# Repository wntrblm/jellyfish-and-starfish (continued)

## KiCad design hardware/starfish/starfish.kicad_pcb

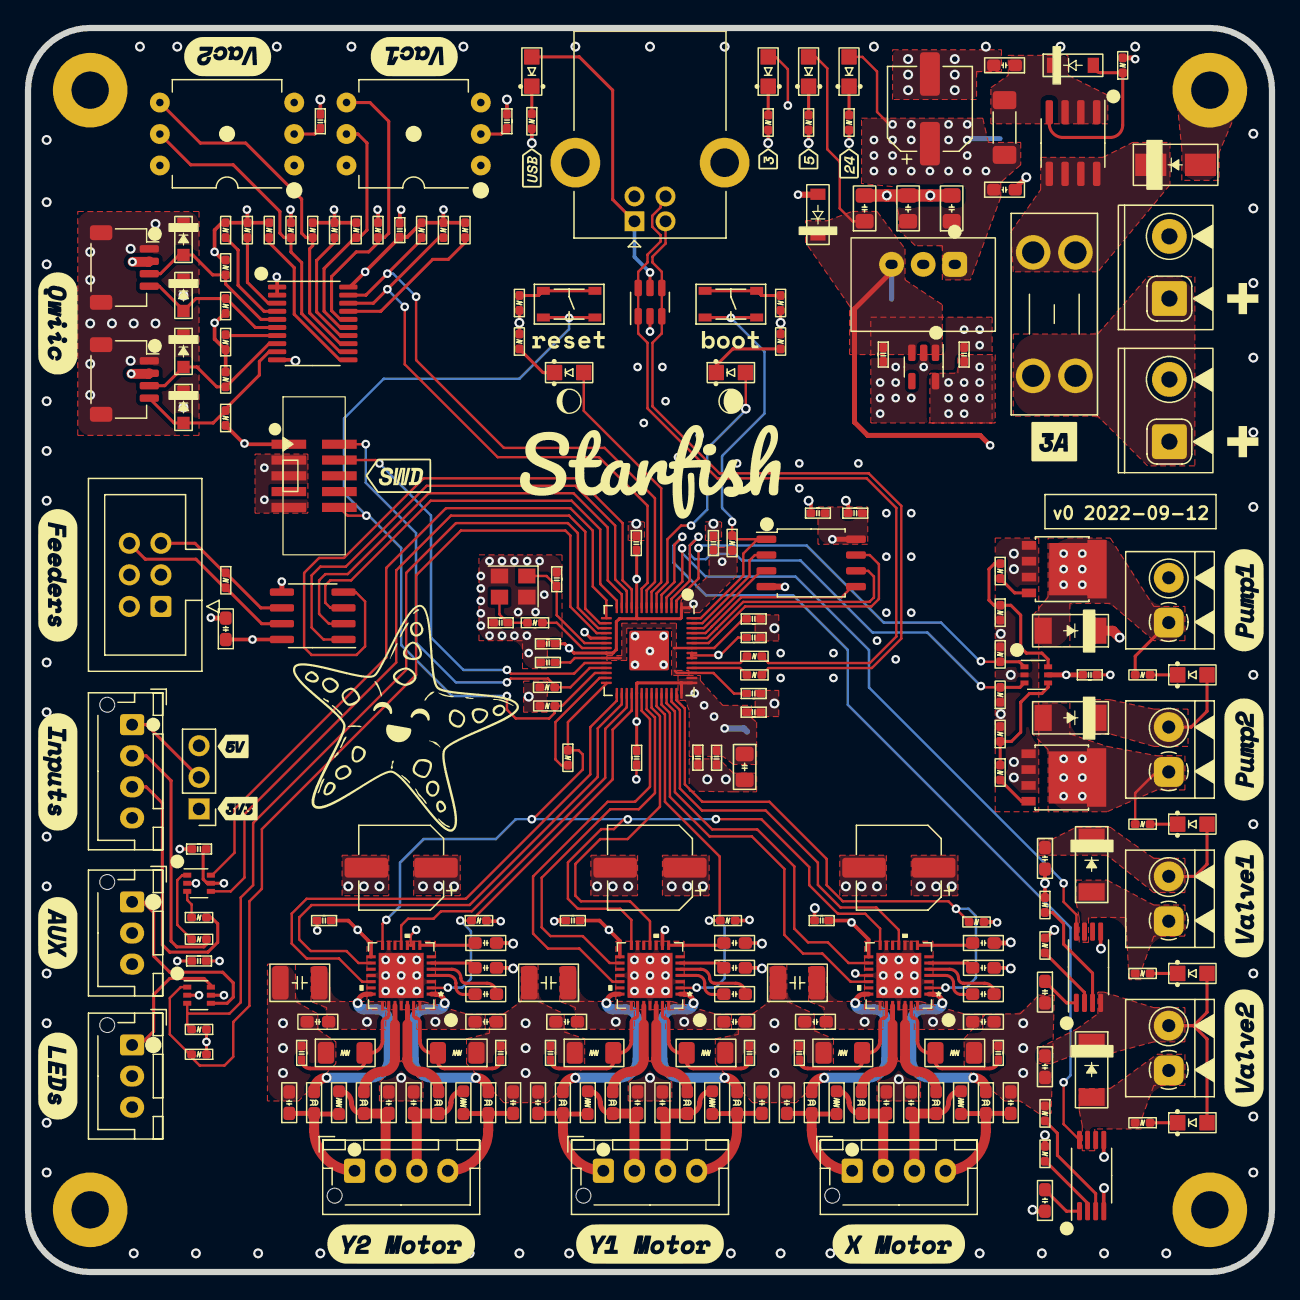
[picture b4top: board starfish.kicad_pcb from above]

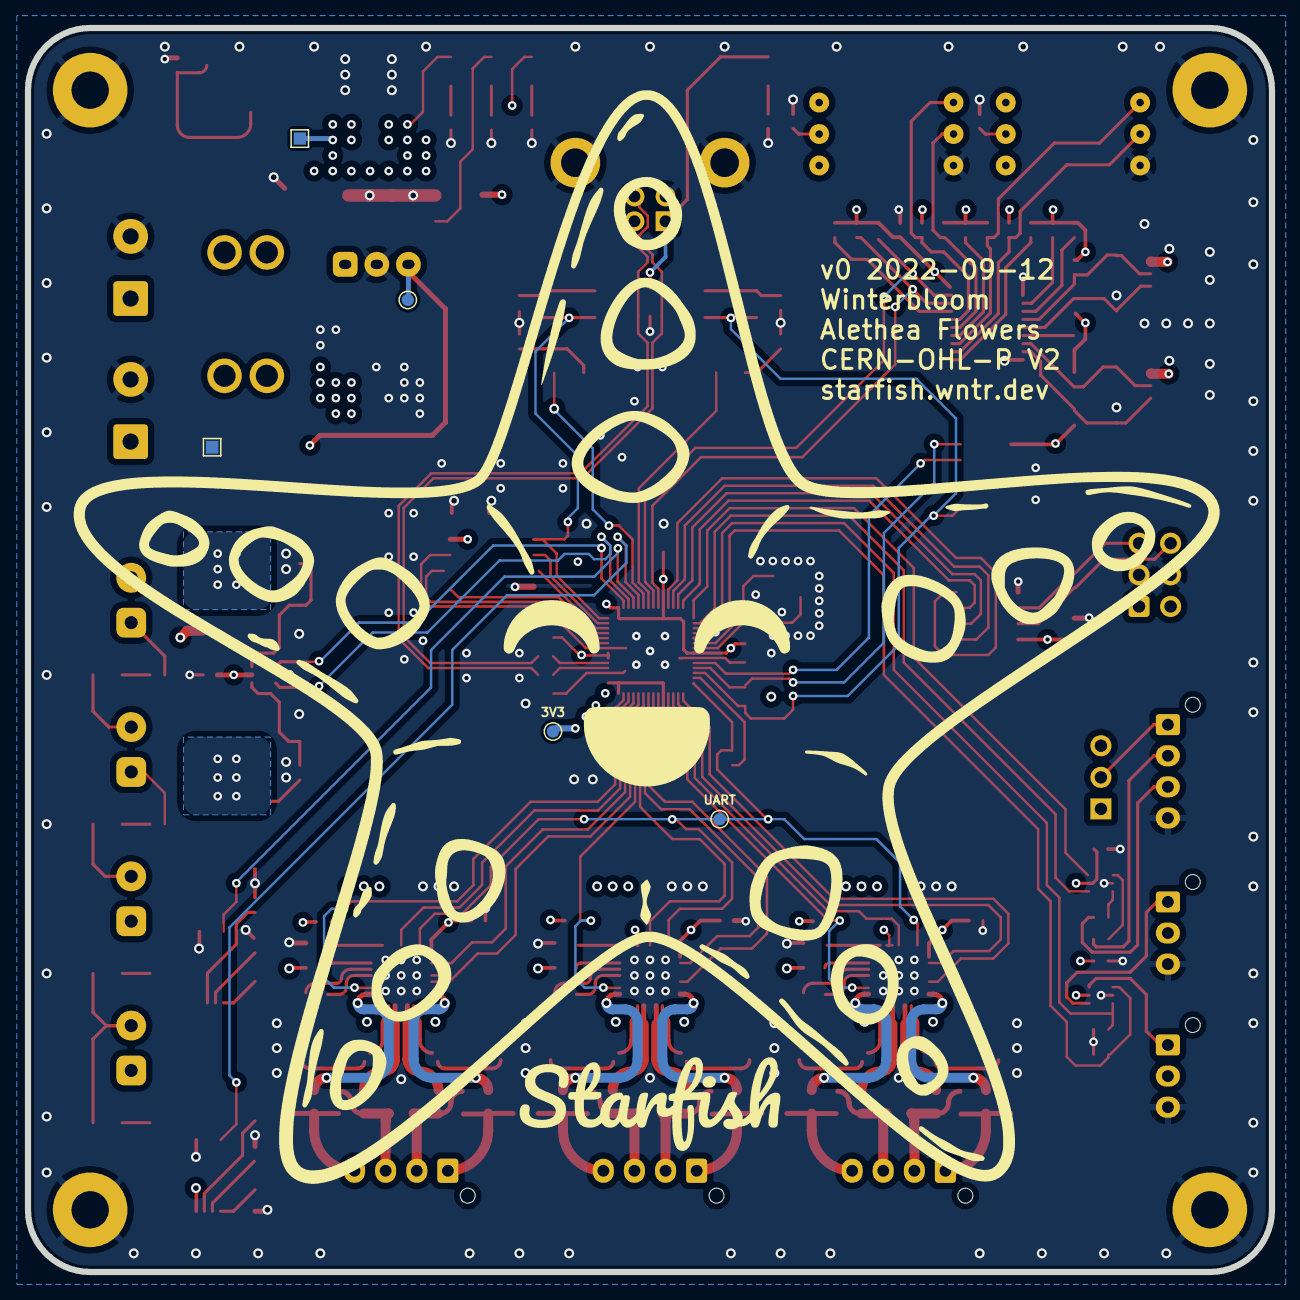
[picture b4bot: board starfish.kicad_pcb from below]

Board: 4 copper layers, 100.0 x 100.0 mm, 228 parts (5 on the bottom side), 147 nets.

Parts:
C201, C202, C801, C1202, C1302, C1403, C1413, C1414, C1503, C1513, C1514, C1603, C1613, C1614: 100n; C_0603_HandSolder
C203, C1411, C1511, C1611: 100u; CP_Elec_6.3x9.9
C206: 4u7; C_0805_HandSolder
C207, C208: 22u; C_0805_HandSolder
C209, C210, C309, C310, C316: 1u; C_0402_HandSolder
C301: 10u; C_0805_HandSolder
C302, C303, C304, C305, C306, C307, C308, C311, C312, C315, C401, C402, C501, C601, C701, C901, C1402, C1405, C1406, C1502, C1505, C1506, C1602, C1605, C1606: 100n; C_0402_HandSolder
C313, C314: 15p; C_0402_HandSolder
C1201, C1301, C1404, C1504, C1604: 4u7; C_0603_HandSolder
C1401, C1501, C1601: 22n; C_0603_HandSolder
C1407, C1408, C1409, C1410, C1507, C1508, C1509, C1510, C1607, C1608, C1609, C1610: 470p; C_0603_HandSolder
C1412, C1512, C1612: 10u; C_1210_HandSolder
D201: SMAJ28A; D_SMA
D202: PDZ16BGWJ; D_SOD-123
D203: 24V; LED_0805_Kingbright_APT2012
D204: 5V; LED_0805_Kingbright_APT2012
D205: 3V3; LED_0805_Kingbright_APT2012
D301: Act; LED_0805_Kingbright_APT2012
D302: Aux; LED_0805_Kingbright_APT2012
D401, D402, D403, D404: PESD5V; D_SOD-323
D405: PMEG2005EGWJ; D_SOD-123
D406: USB; LED_0805_Kingbright_APT2012
D1001, D1101, D1201, D1301: On; LED_0805_Kingbright_APT2012
D1002, D1102, D1202, D1302: PMEG3030EP; D_SOD-128
F201: Fuse; Fuseholder_Blade_Mini_Keystone_3568
FB201: 60R @ 100MHz; L_1806_4516Metric_Pad1.45x1.90mm_HandSolder
FB1401, FB1402, FB1403, FB1404, FB1501, FB1502, FB1503, FB1504, FB1601, FB1602, FB1603, FB1604: 120R @ 100MHz; L_0603_HandSolder
H101, H102, H103, H104: GND; MountingHole_3mm_Pad
J1: SWD; Connector_Cortex_Debug_IDC_2x05_P1.27mm_Vertical_Shrouded_S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
J201: DC in; TerminalBlock_CUI_TB002-500_1x02_P5.00mm_Vertical
J202: DC thru; TerminalBlock_CUI_TB002-500_1x02_P5.00mm_Vertical
J401: Cam LED; JST_XH_B3B-XH-AM_1x03_P2.50mm_Vertical
J402: Aux out; JST_XH_B3B-XH-AM_1x03_P2.50mm_Vertical
J403: Voltage; PinHeader_1x03_P2.54mm_Vertical
J404: Inputs; JST_XH_B4B-XH-AM_1x04_P2.50mm_Vertical
J405, J406: Qwiic; JST_SH_SM04B-SRSS-TB_1x04-1MP_P1.00mm_Horizontal
J407: USB B; USB_B_Receptacle_Horizontal
J801: Feeders; IDC-Header_2x03_P2.54mm_Vertical
J1001, J1101: Pump; TerminalBlock_4UCON_1x02_P3.50mm_Horizontal
J1201, J1301: Valve; TerminalBlock_4UCON_1x02_P3.50mm_Horizontal
J1401, J1501, J1601: Motor; JST_XH_B4B-XH-AM_1x04_P2.50mm_Vertical
Q201: DMP3037LSS-13; SOIC-8_3.9x4.9mm_P1.27mm
Q1001, Q1101: PSMN011-30YLC; LFPAK56
R201, R1202, R1302: 47k; R_0402_HandSolder
R202, R1003, R1103, R1203, R1303: 5k1; R_0402_HandSolder
R203, R204, R305, R306, R307, R308, R309, R310, R405, R1002, R1102: 1k; R_0402_HandSolder
R301, R302, R311, R401, R402, R503, R504, R505, R508, R511, R514, R901, R902, R1401, R1501, R1601: 10k; R_0402_HandSolder
R303, R304: 27R; R_0402_HandSolder
R403, R404, R801: 120R; R_0402_HandSolder
R501, R502, R506, R507, R509, R510, R512, R513, R515, R516: 4k7; R_0402_HandSolder
R1001, R1101: 100k; R_0402_HandSolder
R1201, R1301: 0R; R_0402_HandSolder
R1402, R1403, R1502, R1503, R1602, R1603: 120m; R_1206_HandSolder
RV1401, RV1402, RV1501, RV1502, RV1601, RV1602: MOV; R_0603_HandSolder
SW301: RESET; Tactile_Switch_4.2mm
SW302: BOOTSEL; Tactile_Switch_4.2mm
TP201: GND; TestPoint_Pad_1.0x1.0mm
TP202: 24V; TestPoint_Pad_1.0x1.0mm
TP203: 5V; TestPoint_Pad_D1.0mm
TP204: 3V3; TestPoint_Pad_D1.0mm
TP301: UART; TestPoint_Pad_D1.0mm
U201: VX7805-500; Converter_DCDC_CUI_VX78-500_THT
U202: MIC5317-3.3; SOT-23-5
U301: RP2040; RP2040-QFN-56
U302: W25Q128JVS; SOIC-8_5.23x5.23mm_P1.27mm
U401, U402, U901: 74HC2G34; SOT-363_SC-70-6
U403: TVS; SOT-23-6
U501: PCA9545; TSSOP-20_4.4x6.5mm_P0.65mm
U601, U701: XGZP6857D
U801: MAX3078E; SOIC-8_3.9x4.9mm_P1.27mm
U1201, U1301: DRV120PWR; TSSOP-8_4.4x3mm_P0.65mm
U1401, U1501, U1601: TMC2209; TMC2209-LA
Y301: 12MHz; Crystal_SMD_Abracon_ABM8G-4Pin_3.2x2.5mm

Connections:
+1V1: C310.1, C311.1, C312.1, U301.23 (DVDD), U301.45 (VREG_VOUT), U301.50 (DVDD)
+3V3: C210.1, C301.1, C302.1, C303.1, C304.1, C305.1, C306.1, C307.1, C308.1, C309.1, C315.1, C316.1, C402.1, C501.1, C601.1, C701.1, C801.1, C1402.1, C1502.1, C1602.1, D205.2 (A), J1.1 (VCC), J403.1, J405.2, J406.2, J801.1, J801.2, R301.2, R302.1, R311.2, R501.1, R502.1, R503.1, R504.1, R505.1, R506.1, R507.1, R508.1, R509.1, R510.1, R511.1, R512.1, R513.1, R514.1, R515.1, R516.1, R1401.2, R1501.2, R1601.2, TP204.1, U202.5 (OUT), U301.1 (IOVDD), U301.10 (IOVDD), U301.22 (IOVDD), U301.33 (IOVDD), U301.42 (IOVDD), U301.43 (ADC_AVDD), U301.44 (VREG_IN), U301.48 (USB_VDD), U301.49 (IOVDD), U302.8 (VCC), U402.5 (VCC), U501.20 (VDD), U601.2 (VDD), U701.2 (VDD), U801.8 (VCC), U1401.15 (VCC_IO), U1501.9 (MS1_AD0), U1501.15 (VCC_IO), U1601.9 (MS1_AD0), U1601.10 (MS2_AD1), U1601.15 (VCC_IO)
+5V: C208.1, C209.1, C401.1, C901.1, D204.2 (A), D405.1 (K), J401.2, J402.2, J403.3, TP203.1, U201.3 (Vout), U202.1 (IN), U202.3 (EN), U401.5 (VCC), U901.5 (VCC)
+24V: C202.1, C203.1, C206.1, C207.1, C1202.1, C1302.1, C1403.1, C1411.1, C1412.1, C1413.1, C1414.1, C1503.1, C1511.1, C1512.1, C1513.1, C1514.1, C1603.1, C1611.1, C1612.1, C1613.1, C1614.1, D203.2 (A), D1001.2 (A), D1002.1 (K), D1101.2 (A), D1102.1 (K), D1201.2 (A), D1202.1 (K), D1301.2 (A), D1302.1 (K), FB201.2, J1001.2, J1101.2, J1201.2, J1301.2, TP202.1, U201.1 (Vin), U1201.4 (VIN), U1301.4 (VIN), U1401.22 (VS), U1401.28 (VS), U1501.22 (VS), U1501.28 (VS), U1601.22 (VS), U1601.28 (VS)
/Buffer/IN_A: R901.2, U301.2 (GPIO0), U901.1 (1A)
/Buffer/IN_B: R902.2, U301.3 (GPIO1), U901.3 (2A)
/Buffer/OUT_A: R1001.1, R1002.1, U901.6 (1Y)
/Buffer/OUT_B: R1101.1, R1102.1, U901.4 (2Y)
/Connections/AUX OUT: J402.1, U401.4 (2Y)
/Connections/AUX_OUT: R402.2, U301.17 (GPIO14), U401.3 (2A)
/Connections/CAM LED OUT: J401.1, U401.6 (1Y)
/Connections/CAM_LED: R401.2, U301.18 (GPIO15), U401.1 (1A)
/Connections/IN_1: U301.15 (GPIO12), U402.6 (1Y)
/Connections/IN_2: U301.16 (GPIO13), U402.4 (2Y)
/Connections/MCU_D+: J407.3 (D+), R303.1, U403.1 (D-), U403.6 (D-)
/Connections/MCU_D-: J407.2 (D-), R304.1, U403.3 (D+), U403.4 (D+)
/Connections/QWIIC1_SCK: D403.2 (A2), J405.4, R507.2, U501.6 (SC0)
/Connections/QWIIC1_SDA: D401.2 (A2), J405.3, R506.2, U501.5 (SD0)
/Connections/QWIIC2_SCK: D404.2 (A2), J406.4, R510.2, U501.9 (SC1)
/Connections/QWIIC2_SDA: D402.2 (A2), J406.3, R509.2, U501.8 (SD1)
/I2C Multiplexer/INT: R503.2, U501.17 (~INT)
/I2C Multiplexer/SCL2: R513.2, U501.13 (SC2), U701.4 (SDA)
/I2C Multiplexer/SCL3: R516.2, U501.16 (SC3), U601.4 (SDA)
/I2C Multiplexer/SDA2: R512.2, U501.12 (SD2), U701.5 (SCL)
/I2C Multiplexer/SDA3: R515.2, U501.15 (SD3), U601.5 (SCL)
/I2C Multiplexer/~INT0: R505.2, U501.4 (~INT0)
/I2C Multiplexer/~INT1: R508.2, U501.7 (~INT1)
/I2C Multiplexer/~INT2: R511.2, U501.11 (~INT2)
/I2C Multiplexer/~INT3: R514.2, U501.14 (~INT3)
/I2C Multiplexer/~RESET: R504.2, U501.3 (~RESET)
/Microcontroller/ACT_LED: D301.2 (A), U301.7 (GPIO5)
/Microcontroller/AUX_LED: D302.2 (A), U301.6 (GPIO4)
/Microcontroller/I2C1_SCL: R501.2, U301.9 (GPIO7), U501.18 (SCL)
/Microcontroller/I2C1_SDA: R502.2, U301.8 (GPIO6), U501.19 (SDA)
/Microcontroller/M0_DIAG: U301.40 (GPIO28_ADC2), U1401.11 (DIAG)
/Microcontroller/M0_DIR: U301.38 (GPIO26_ADC0), U1401.19 (DIR)
/Microcontroller/M0_EN: R1401.1, U301.41 (GPIO29_ADC3), U1401.2 (ENN)
/Microcontroller/M0_STEP: U301.39 (GPIO27_ADC1), U1401.16 (STEP)
/Microcontroller/M1_DIAG: U301.36 (GPIO24), U1501.11 (DIAG)
/Microcontroller/M1_DIR: U301.34 (GPIO22), U1501.19 (DIR)
/Microcontroller/M1_EN: R1501.1, U301.37 (GPIO25), U1501.2 (ENN)
/Microcontroller/M1_STEP: U301.35 (GPIO23), U1501.16 (STEP)
/Microcontroller/M2_DIAG: U301.31 (GPIO20), U1601.11 (DIAG)
/Microcontroller/M2_DIR: U301.29 (GPIO18), U1601.19 (DIR)
/Microcontroller/M2_EN: R1601.1, U301.32 (GPIO21), U1601.2 (ENN)
/Microcontroller/M2_STEP: U301.30 (GPIO19), U1601.16 (STEP)
/Microcontroller/QSPI_CS: R311.1, SW302.1, U301.56 (QSPI_SS), U302.1 (~CS)
/Microcontroller/QSPI_SCLK: U301.52 (QSPI_SCLK), U302.6 (CLK)
/Microcontroller/QSPI_SD0: U301.53 (QSPI_SD0), U302.5 (DI(IO0))
/Microcontroller/QSPI_SD1: U301.55 (QSPI_SD1), U302.2 (DO(IO1))
/Microcontroller/QSPI_SD2: U301.54 (QSPI_SD2), U302.3 (IO2)
/Microcontroller/QSPI_SD3: U301.51 (QSPI_SD3), U302.7 (IO3)
/Microcontroller/RS485_OUT_EN: U301.14 (GPIO11), U801.3 (DE)
/Microcontroller/RS485_~IN_EN: U301.13 (GPIO10), U801.2 (~RE)
/Microcontroller/RUN: J1.10 (~RESET), R301.1, SW301.1, U301.26 (RUN)
/Microcontroller/SWCLK: J1.4 (SWCLK), U301.24 (SWCLK)
/Microcontroller/SWD: J1.2 (SWDIO), R302.2, U301.25 (SWD)
/Microcontroller/UART0_TX: R305.2, U301.27 (GPIO16)
/Microcontroller/UART1_RX: U301.12 (GPIO9), U801.1 (RO)
/Microcontroller/UART1_TX: U301.11 (GPIO8), U801.4 (DI)
/Microcontroller/VALVE_A: U301.4 (GPIO2), U1201.8 (EN)
/Microcontroller/VALVE_B: U301.5 (GPIO3), U1301.8 (EN)
/Microcontroller/XIN: C313.1, U301.20 (XIN), Y301.1
/Microcontroller/XOUT: R310.1, U301.21 (XOUT)
/Power/DCIN: F201.1, J201.1, J202.1
/Power/gate: D202.2 (A), Q201.4 (G), R201.1
/Power/post fuse: D201.1 (K), F201.2, Q201.5 (D), Q201.6 (D), Q201.7 (D), Q201.8 (D)
/Power/post polarity: C201.1, D202.1 (K), FB201.1, Q201.1 (S), Q201.2 (S), Q201.3 (S)
/Pump A/switched: D1002.2 (A), J1001.1, Q1001.5 (D), R1003.2
/Pump B/switched: D1102.2 (A), J1101.1, Q1101.5 (D), R1103.2
/RS485/RS-485+: J801.5, R801.1, U801.6 (A)
/RS485/RS-485-: J801.6, R801.2, U801.7 (B)
/TMC_UART: R305.1, TP301.1, U301.28 (GPIO17), U1401.14 (PDN_UART), U1501.14 (PDN_UART), U1601.14 (PDN_UART)
/Valve A/KEEP: C1201.1, U1201.1 (KEEP)
/Valve A/OSC: R1201.2, U1201.3 (OSC)
/Valve A/PEAK: R1202.2, U1201.2 (PEAK)
/Valve A/switched: D1202.2 (A), J1201.1, R1203.2, U1201.7 (OUT)
/Valve B/KEEP: C1301.1, U1301.1 (KEEP)
/Valve B/OSC: R1301.2, U1301.3 (OSC)
/Valve B/PEAK: R1302.2, U1301.2 (PEAK)
/Valve B/switched: D1302.2 (A), J1301.1, R1303.2, U1301.7 (OUT)
/X Motor/5VOUT: C1404.1, U1401.8 (5VOUT)
/X Motor/BRA: C1406.1, R1403.2, U1401.23 (BRA)
/X Motor/BRB: C1405.1, R1402.2, U1401.27 (BRB)
/X Motor/CPI: C1401.2, U1401.5 (CPI)
/X Motor/CPO: C1401.1, U1401.4 (CPO)
/X Motor/OA1: FB1403.1, U1401.24 (OA1)
/X Motor/OA2: FB1404.1, U1401.21 (OA2)
/X Motor/OB1: FB1402.1, U1401.26 (OB1)
/X Motor/OB2: FB1401.1, U1401.1 (OB2)
/X Motor/VCP: C1403.2, U1401.6 (VCP)
/Y1 Motor/5VOUT: C1504.1, U1501.8 (5VOUT)
/Y1 Motor/BRA: C1506.1, R1503.2, U1501.23 (BRA)
/Y1 Motor/BRB: C1505.1, R1502.2, U1501.27 (BRB)
/Y1 Motor/CPI: C1501.2, U1501.5 (CPI)
/Y1 Motor/CPO: C1501.1, U1501.4 (CPO)
/Y1 Motor/OA1: FB1503.1, U1501.24 (OA1)
/Y1 Motor/OA2: FB1504.1, U1501.21 (OA2)
/Y1 Motor/OB1: FB1502.1, U1501.26 (OB1)
/Y1 Motor/OB2: FB1501.1, U1501.1 (OB2)
/Y1 Motor/VCP: C1503.2, U1501.6 (VCP)
/Y2 Motor/5VOUT: C1604.1, U1601.8 (5VOUT)
/Y2 Motor/BRA: C1606.1, R1603.2, U1601.23 (BRA)
/Y2 Motor/BRB: C1605.1, R1602.2, U1601.27 (BRB)
/Y2 Motor/CPI: C1601.2, U1601.5 (CPI)
/Y2 Motor/CPO: C1601.1, U1601.4 (CPO)
/Y2 Motor/OA1: FB1603.1, U1601.24 (OA1)
/Y2 Motor/OA2: FB1604.1, U1601.21 (OA2)
/Y2 Motor/OB1: FB1602.1, U1601.26 (OB1)
/Y2 Motor/OB2: FB1601.1, U1601.1 (OB2)
/Y2 Motor/VCP: C1603.2, U1601.6 (VCP)
GND: C201.2, C202.2, C203.2, C206.2, C207.2, C208.2, C209.2, C210.2, C301.2, C302.2, C303.2, C304.2, C305.2, C306.2, C307.2, C308.2, C309.2, C310.2, C311.2, C312.2, C313.2, C314.2, C315.2, C316.2, C401.2, C402.2, C501.2, C601.2, C701.2, C801.2, C901.2, C1201.2, C1202.2, C1301.2, C1302.2, C1402.2, C1404.2, C1405.2, C1406.2, C1407.2, C1408.2, C1409.2, C1410.2, C1411.2, C1412.2, C1413.2, C1414.2, C1502.2, C1504.2, C1505.2, C1506.2, C1507.2, C1508.2, C1509.2, C1510.2, C1511.2, C1512.2, C1513.2, C1514.2, C1602.2, C1604.2, C1605.2, C1606.2, C1607.2, C1608.2, C1609.2, C1610.2, C1611.2, C1612.2, C1613.2, C1614.2, D201.2 (A), D401.1 (A1), D402.1 (A1), D403.1 (A1), D404.1 (A1), H101.1, H102.1, H103.1, H104.1, J1.3 (GND), J1.5 (GND), J1.9 (GNDDetect), J201.2, J202.2, J401.3, J402.3, J404.4, J405.1, J405.MP (MountPin), J406.1, J406.MP (MountPin), J407.4 (GND), J407.5 (Shield), J801.3, J801.4, Q1001.1 (S), Q1001.2 (S), Q1001.3 (S), Q1101.1 (S), Q1101.2 (S), Q1101.3 (S), R201.2, R202.2, R203.2, R204.2, R306.1, R307.1, R308.2, R309.2, R401.1, R402.1, R405.2, R901.1, R902.1, R1001.2, R1101.2, R1201.1, R1202.1, R1301.1, R1302.1, R1402.1, R1403.1, R1502.1, R1503.1, R1602.1, R1603.1, TP201.1, U201.2 (GND), U202.2 (GND), U301.19 (TESTEN), U301.57 (GND), U302.4 (GND), U401.2 (GND), U402.2 (GND), U403.2 (GND), U501.1 (A0), U501.2 (A1), U501.10 (VSS), U601.6 (GND), U701.6 (GND), U801.5 (GND), U901.2 (GND), U1201.5 (GND), U1301.5 (GND), U1401.3 (GND), U1401.9 (MS1_AD0), U1401.10 (MS2_AD1), U1401.13 (CLK), U1401.18 (GND), U1401.25 (GND), U1401.29 (PAD), U1501.3 (GND), U1501.10 (MS2_AD1), U1501.13 (CLK), U1501.18 (GND), U1501.25 (GND), U1501.29 (PAD), U1601.3 (GND), U1601.13 (CLK), U1601.18 (GND), U1601.25 (GND), U1601.29 (PAD), Y301.2, Y301.4
unnamed: C314.1, R310.2, Y301.3
unnamed: C1407.1, FB1402.2, J1401.3, RV1401.2
unnamed: C1408.1, FB1404.2, J1401.1, RV1402.2
unnamed: C1409.1, FB1401.2, J1401.4, RV1401.1
unnamed: C1410.1, FB1403.2, J1401.2, RV1402.1
unnamed: C1507.1, FB1502.2, J1501.3, RV1501.2
unnamed: C1508.1, FB1504.2, J1501.1, RV1502.2
unnamed: C1509.1, FB1501.2, J1501.4, RV1501.1
unnamed: C1510.1, FB1503.2, J1501.2, RV1502.1
unnamed: C1607.1, FB1602.2, J1601.3, RV1601.2
unnamed: C1608.1, FB1604.2, J1601.1, RV1602.2
unnamed: C1609.1, FB1601.2, J1601.4, RV1601.1
unnamed: C1610.1, FB1603.2, J1601.2, RV1602.1
unnamed: D203.1 (K), R202.1
unnamed: D204.1 (K), R203.1
unnamed: D205.1 (K), R204.1
unnamed: D301.1 (K), R308.1
unnamed: D302.1 (K), R309.1
unnamed: D405.2 (A), D406.2 (A), J407.1 (VBUS), U403.5 (VBUS)
unnamed: D406.1 (K), R405.1
unnamed: D1001.1 (K), R1003.1
unnamed: D1101.1 (K), R1103.1
unnamed: D1201.1 (K), R1203.1
unnamed: D1301.1 (K), R1303.1
unnamed: J403.2, J404.1
unnamed: J404.2, R403.2
unnamed: J404.3, R404.2
unnamed: Q1001.4 (G), R1002.2
unnamed: Q1101.4 (G), R1102.2
unnamed: R303.2, U301.47 (USB_DP)
unnamed: R304.2, U301.46 (USB_DM)
unnamed: R306.2, SW301.2
unnamed: R307.2, SW302.2
unnamed: R403.1, U402.1 (1A)
unnamed: R404.1, U402.3 (2A)

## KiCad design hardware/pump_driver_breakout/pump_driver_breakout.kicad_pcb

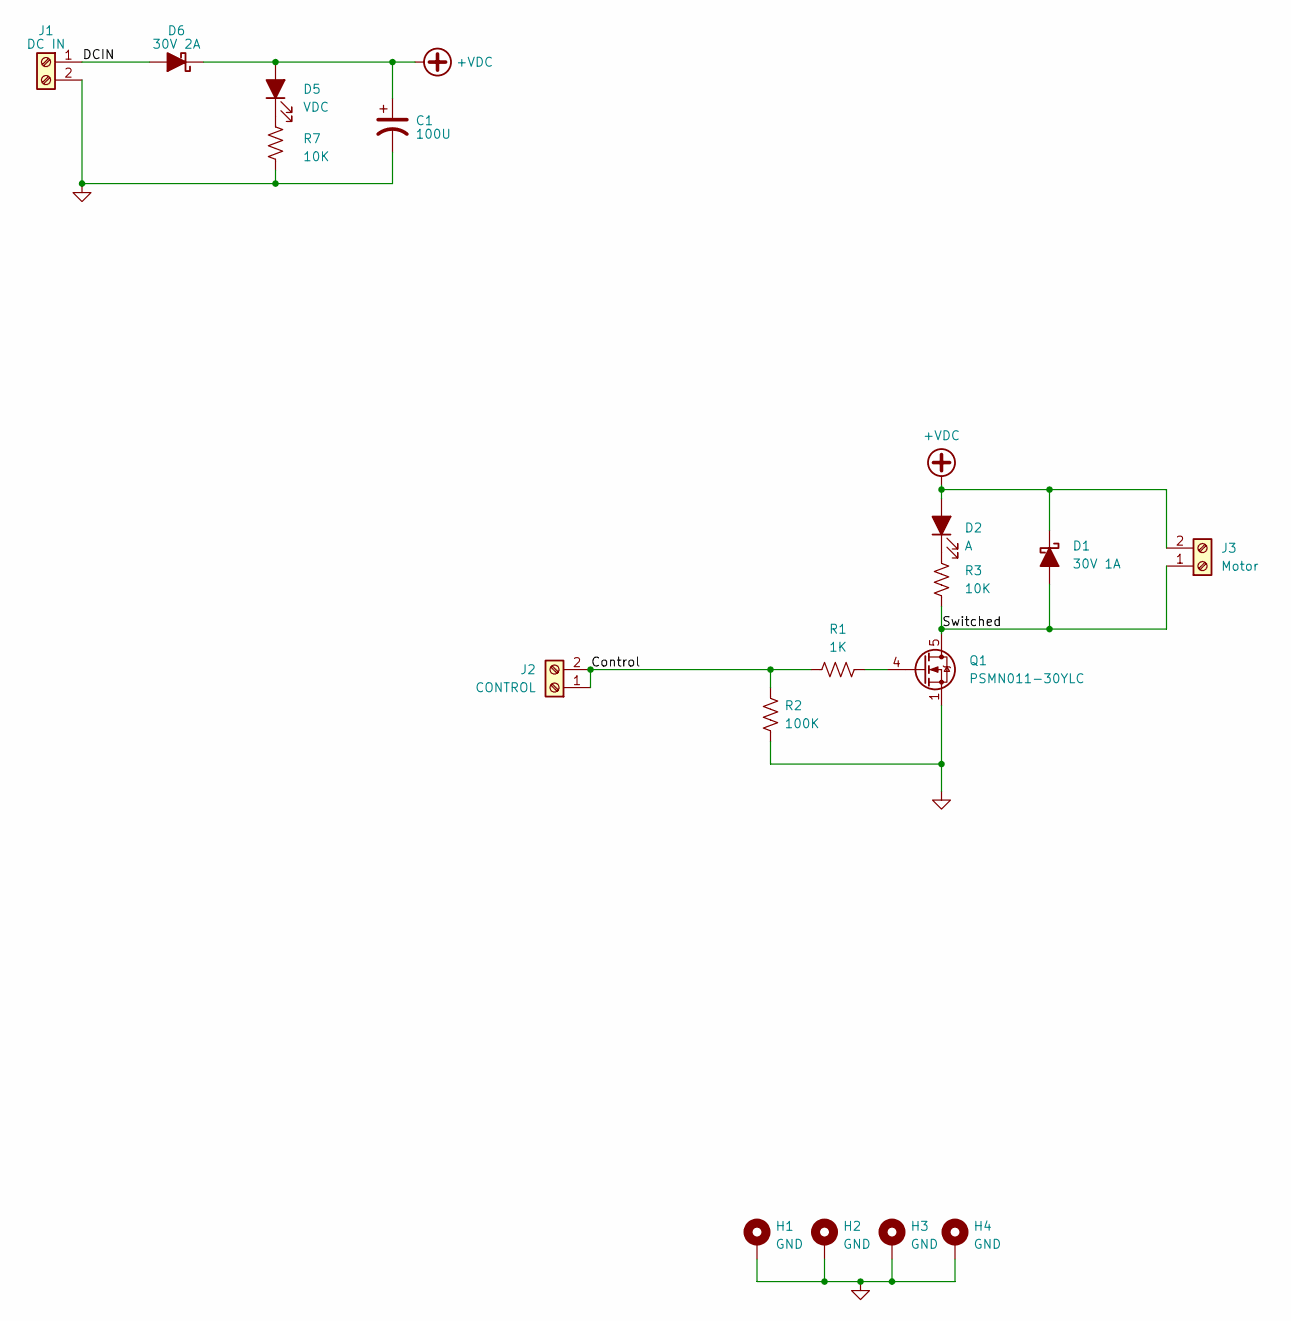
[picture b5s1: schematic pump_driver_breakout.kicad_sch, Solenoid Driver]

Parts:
C1: 100U; C_1210_3225Metric_Pad1.33x2.70mm_HandSolder
D1: 30V 1A; D_SOD-128
D2: A; LED_0805_Kingbright_APT2012; mpn APT2012EC
D5: VDC; LED_0805_Kingbright_APT2012; mpn APT2012EC
D6: 30V 2A; D_SOD-128
H1, H2, H3, H4: GND; MountingHole_3mm_Pad
J1: DC IN; TerminalBlock_4UCON_1x02_P3.50mm_Horizontal
J2: CONTROL; TerminalBlock_4UCON_1x02_P3.50mm_Horizontal
J3: Motor; TerminalBlock_4UCON_1x02_P3.50mm_Horizontal
Q1: PSMN011-30YLC; LFPAK56
R1: 1K; R_0603_1608Metric_Pad0.98x0.95mm_HandSolder
R2: 100K; R_0603_1608Metric_Pad0.98x0.95mm_HandSolder
R3, R7: 10K; R_0603_1608Metric_Pad0.98x0.95mm_HandSolder; mpn AC0603FR-075K1L

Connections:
+VDC: C1.1, D1.1 (K), D2.2 (A), D5.2 (A), D6.1 (K), J3.2
/Control: J2.1, J2.2, R1.1, R2.1
/DCIN: D6.2 (A), J1.1
/Switched: D1.2 (A), J3.1, Q1.5 (D), R3.2
GND: C1.2, H1.1, H2.1, H3.1, H4.1, J1.2, Q1.1 (S), Q1.2 (S), Q1.3 (S), R2.2, R7.2
unnamed: D2.1 (K), R3.1
unnamed: D5.1 (K), R7.1
unnamed: Q1.4 (G), R1.2

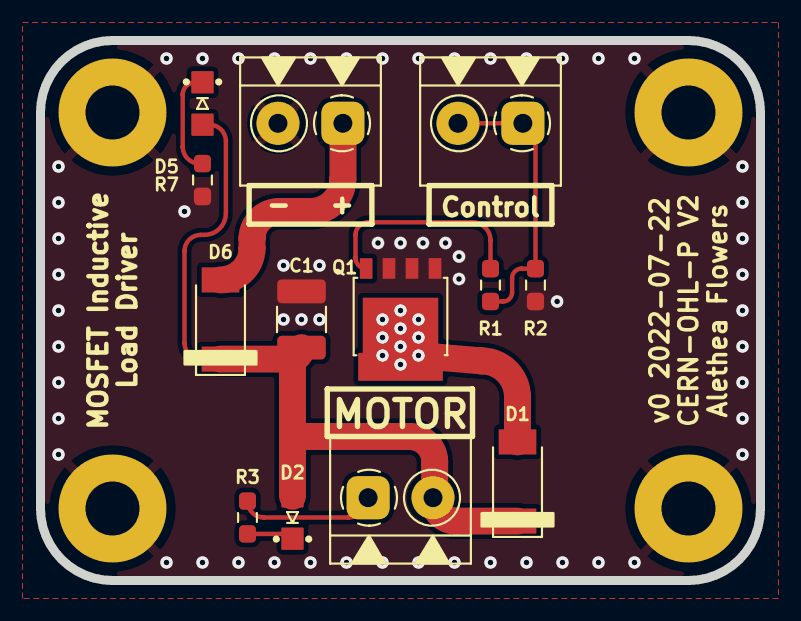
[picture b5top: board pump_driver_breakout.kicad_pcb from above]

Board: 2 copper layers, 40.0 x 30.0 mm, 17 parts (0 on the bottom side), 8 nets.

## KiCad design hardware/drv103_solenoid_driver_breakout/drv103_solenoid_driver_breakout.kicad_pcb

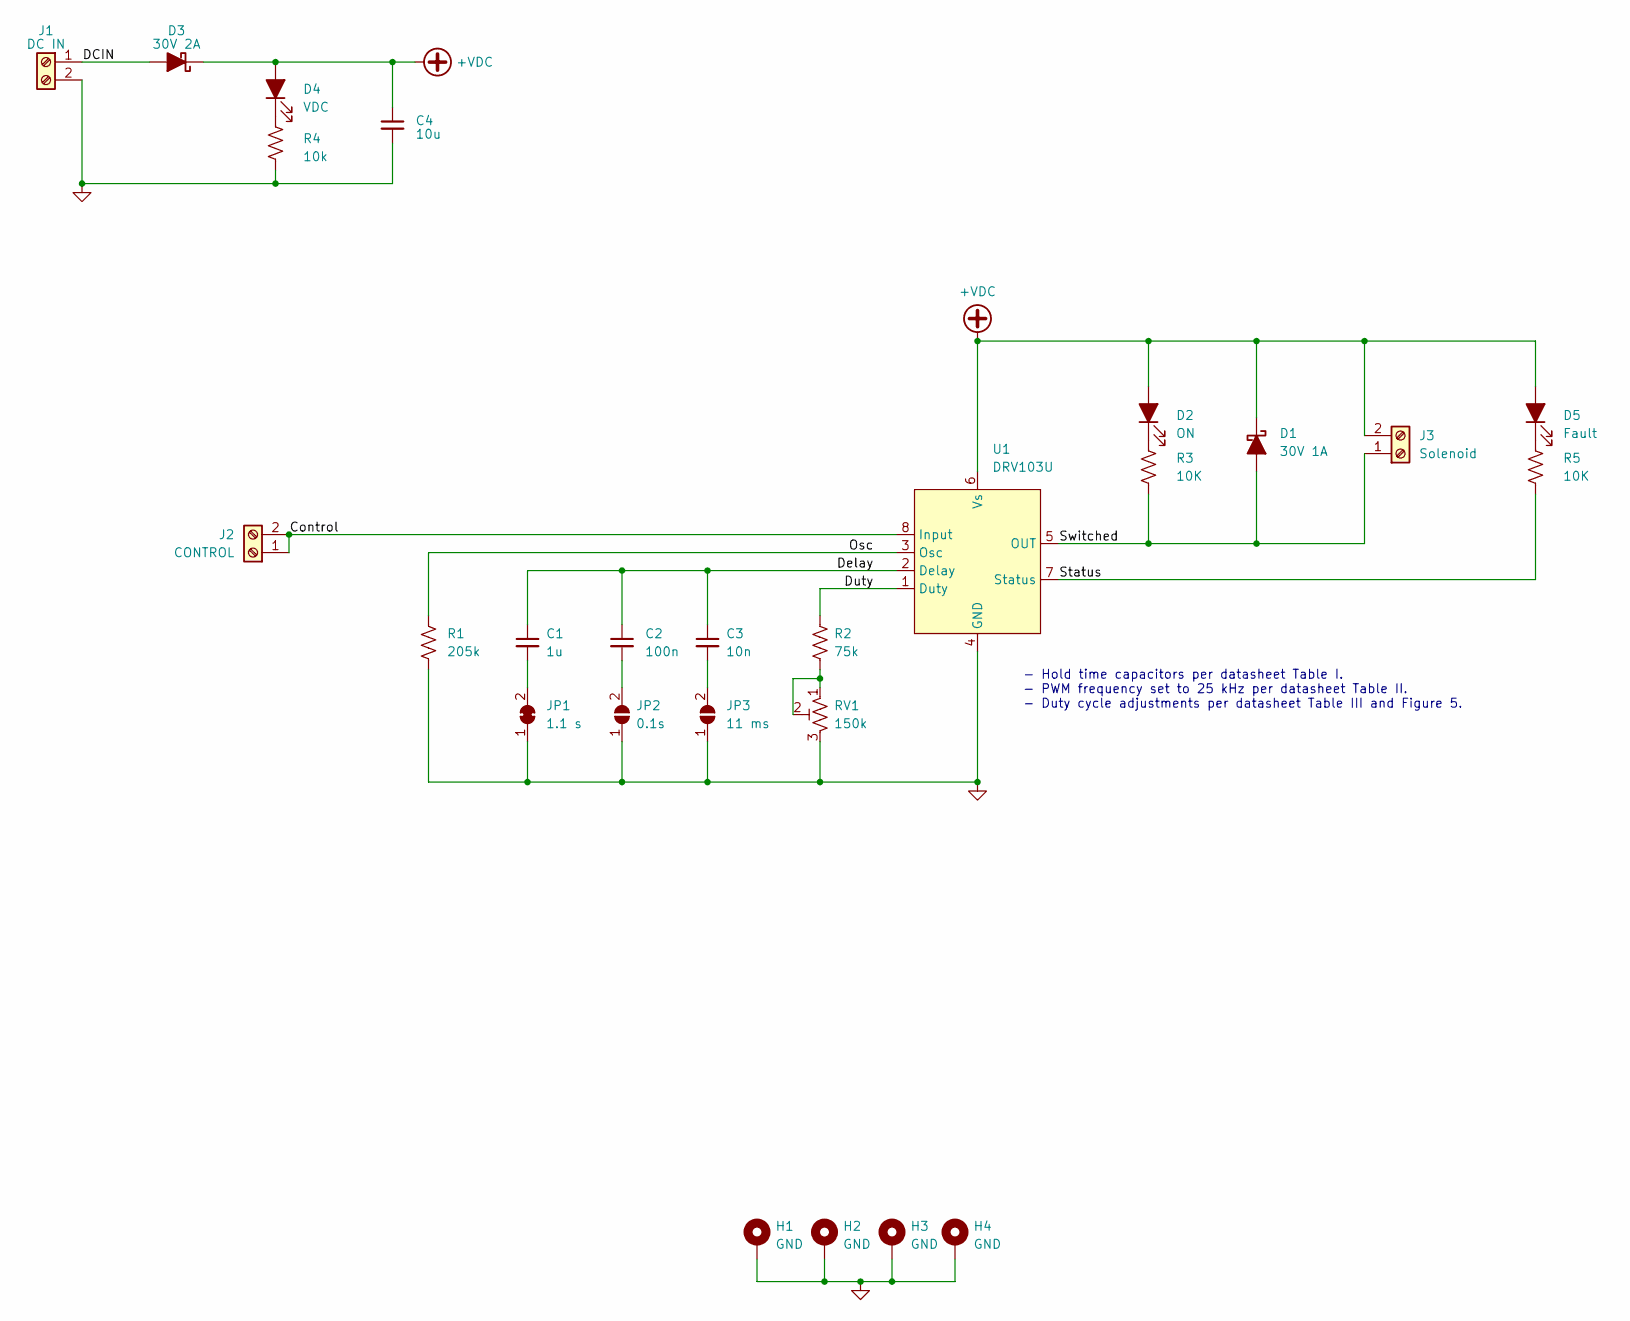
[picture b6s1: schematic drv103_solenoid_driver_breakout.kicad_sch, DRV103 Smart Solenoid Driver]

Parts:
C1: 1u; C_0603_1608Metric_Pad1.08x0.95mm_HandSolder
C2: 100n; C_0603_1608Metric_Pad1.08x0.95mm_HandSolder
C3: 10n; C_0603_1608Metric_Pad1.08x0.95mm_HandSolder
C4: 10u; C_0805_2012Metric_Pad1.18x1.45mm_HandSolder
D1: 30V 1A; D_SOD-128
D2: ON; LED_0805_Kingbright_APT2012; mpn APT2012EC
D3: 30V 2A; D_SOD-128
D4: VDC; LED_0805_Kingbright_APT2012; mpn APT2012EC
D5: Fault; LED_0805_Kingbright_APT2012; mpn APT2012EC
H1, H2, H3, H4: GND; MountingHole_3mm_Pad
J1: DC IN; TerminalBlock_4UCON_1x02_P3.50mm_Horizontal
J2: CONTROL; TerminalBlock_4UCON_1x02_P3.50mm_Horizontal
J3: Solenoid; TerminalBlock_4UCON_1x02_P3.50mm_Horizontal
JP1: 1.1 s; SolderJumper-2_P1.3mm_Bridged_RoundedPad1.0x1.5mm
JP2: 0.1s; SolderJumper-2_P1.3mm_Open_RoundedPad1.0x1.5mm
JP3: 11 ms; SolderJumper-2_P1.3mm_Open_RoundedPad1.0x1.5mm
R1: 205k; R_0603_1608Metric_Pad0.98x0.95mm_HandSolder
R2: 75k; R_0603_1608Metric_Pad0.98x0.95mm_HandSolder
R3, R5: 10K; R_0603_1608Metric_Pad0.98x0.95mm_HandSolder; mpn AC0603FR-075K1L
R4: 10k; R_0603_1608Metric_Pad0.98x0.95mm_HandSolder; mpn AC0603FR-075K1L
RV1: 150k; Potentiometer_Bourns_TC33X_Vertical; mpn TC33X-2-504E
U1: DRV103U; SOIC-8_3.9x4.9mm_P1.27mm; mpn DRV103U

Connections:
+VDC: C4.1, D1.1 (K), D2.2 (A), D3.1 (K), D4.2 (A), D5.2 (A), J3.2, U1.6 (Vs)
/Control: J2.1, J2.2, U1.8 (Input)
/DCIN: D3.2 (A), J1.1
/Delay: C1.1, C2.1, C3.1, U1.2 (Delay)
/Duty: R2.2, U1.1 (Duty)
/Osc: R1.2, U1.3 (Osc)
/Status: R5.2, U1.7 (Status)
/Switched: D1.2 (A), J3.1, R3.2, U1.5 (OUT)
GND: C4.2, H1.1, H2.1, H3.1, H4.1, J1.2, JP1.1 (A), JP2.1 (A), JP3.1 (A), R1.1, R4.2, RV1.3, U1.4 (GND)
unnamed: C1.2, JP1.2 (B)
unnamed: C2.2, JP2.2 (B)
unnamed: C3.2, JP3.2 (B)
unnamed: D2.1 (K), R3.1
unnamed: D4.1 (K), R4.1
unnamed: D5.1 (K), R5.1
unnamed: R2.1, RV1.1, RV1.2

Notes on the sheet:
- Hold time capacitors per datasheet Table I. - PWM frequency set to 25 kHz per datasheet Table II. - Duty cycle adjustments per datasheet Table III and Figure 5.

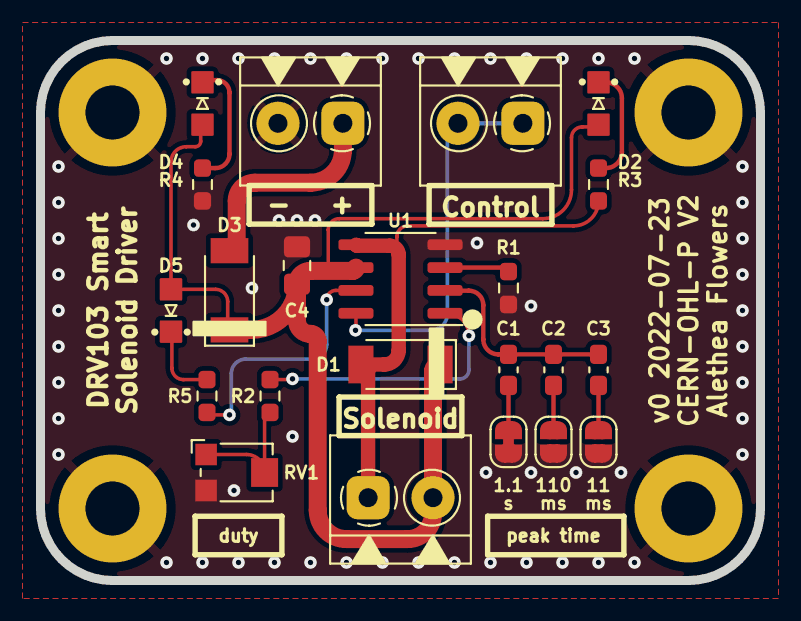
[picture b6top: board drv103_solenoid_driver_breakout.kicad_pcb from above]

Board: 2 copper layers, 40.0 x 30.0 mm, 26 parts (0 on the bottom side), 16 nets.

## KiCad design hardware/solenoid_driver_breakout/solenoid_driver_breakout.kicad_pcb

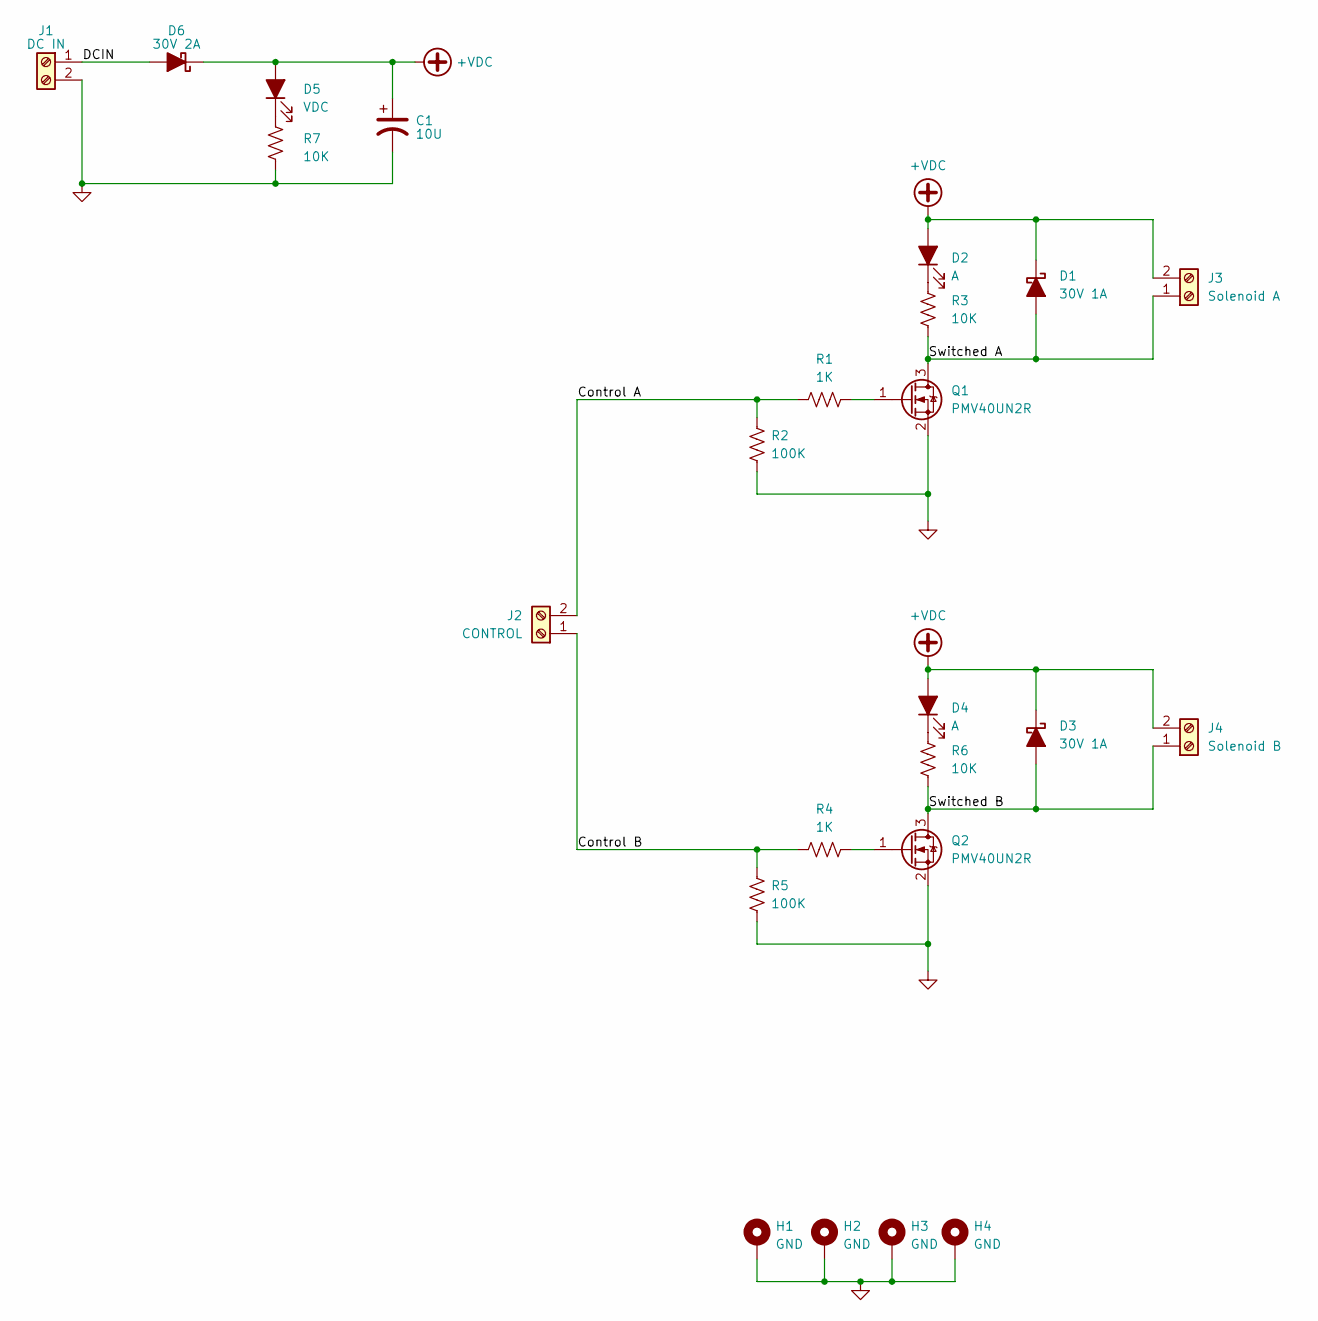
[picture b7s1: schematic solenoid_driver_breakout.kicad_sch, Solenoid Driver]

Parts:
C1: 10U; C_0805_2012Metric_Pad1.18x1.45mm_HandSolder
D1, D3: 30V 1A; D_SOD-128
D2, D4: A; LED_0805_Kingbright_APT2012; mpn APT2012EC
D5: VDC; LED_0805_Kingbright_APT2012; mpn APT2012EC
D6: 30V 2A; D_SOD-128
H1, H2, H3, H4: GND; MountingHole_3mm_Pad
J1: DC IN; TerminalBlock_4UCON_1x02_P3.50mm_Horizontal
J2: CONTROL; TerminalBlock_4UCON_1x02_P3.50mm_Horizontal
J3: Solenoid A; TerminalBlock_4UCON_1x02_P3.50mm_Horizontal
J4: Solenoid B; TerminalBlock_4UCON_1x02_P3.50mm_Horizontal
Q1, Q2: PMV40UN2R; SOT-23
R1, R4: 1K; R_0603_1608Metric_Pad0.98x0.95mm_HandSolder
R2, R5: 100K; R_0603_1608Metric_Pad0.98x0.95mm_HandSolder
R3, R6, R7: 10K; R_0603_1608Metric_Pad0.98x0.95mm_HandSolder; mpn AC0603FR-075K1L

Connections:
+VDC: C1.1, D1.1 (K), D2.2 (A), D3.1 (K), D4.2 (A), D5.2 (A), D6.1 (K), J3.2, J4.2
/Control A: J2.2, R1.1, R2.1
/Control B: J2.1, R4.1, R5.1
/DCIN: D6.2 (A), J1.1
/Switched A: D1.2 (A), J3.1, Q1.3 (D), R3.2
/Switched B: D3.2 (A), J4.1, Q2.3 (D), R6.2
GND: C1.2, H1.1, H2.1, H3.1, H4.1, J1.2, Q1.2 (S), Q2.2 (S), R2.2, R5.2, R7.2
unnamed: D2.1 (K), R3.1
unnamed: D5.1 (K), R7.1
unnamed: Q1.1 (G), R1.2
unnamed: Q2.1 (G), R4.2
unnamed: D4.1 (K), R6.1

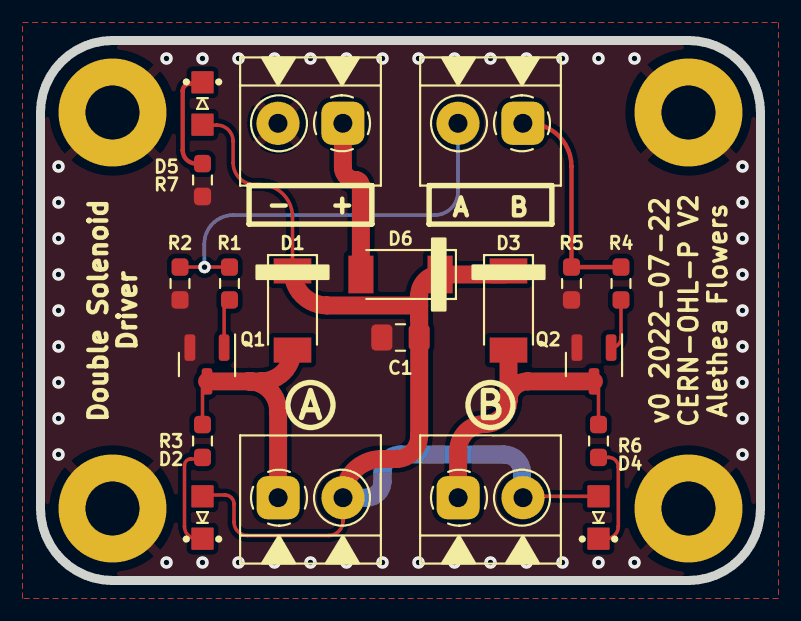
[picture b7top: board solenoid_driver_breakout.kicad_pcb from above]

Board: 2 copper layers, 40.0 x 30.0 mm, 24 parts (0 on the bottom side), 12 nets.

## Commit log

2022-07-09 Initial version
2022-07-09 Add references
2022-07-10 Switch to power module
2022-07-22 Initial sketch for solenoid driver breakout
2022-07-22 Switch solenoid driver to dual low-side switches
2022-07-22 Add mechanical parts
2022-07-23 Add pump driver breakout
2022-07-23 Add smart solenoid drivers
2022-07-27 v1 revision to the schematic
2022-07-27 Footprints assigned
2022-07-28 Finish up layout for v1, ended up removing some stuff
2022-07-28 Add buddy board schematic to references
2022-08-28 Add actual component values
2022-08-28 Add dimensions
2022-08-28 Update x-gantry-back to match head board
2022-09-08 V2 of the head board (Jellyfish)
2022-09-08 V1 of the tailboard
2022-09-08 Replace veritcal connectors with horizontal ones
2022-09-09 Rename head_board to jellyfish
2022-09-09 Move breakouts into a subdirectory
2022-09-09 Rename tail_board to jellyfish_tailboard
2022-09-09 Remove unused footprints
2022-09-09 More cleanup
2022-09-09 Clone jellyfish to starfish
2022-09-10 First pass at schematic for starfish
2022-09-10 Mostly finished starfish schematic, ready for layout!
2022-09-11 Update spacing between top and bottom mounting holes
2022-09-12 First pass at layout and routing
2022-09-12 Cleanup a bit
2022-09-13 Layout and routing mostly done! Just gotta make it prettier!
2022-09-13 I think it might be (99%) done!
2022-09-13 Redo ground stitching
2022-09-13 Add ground pour to incu2
2022-09-13 Add dimensions and such
2022-09-13 Run through purchasing, update some cap sizes
2022-09-14 Update Jellyfish with some stuff from Starfish
2022-09-14 touchup tailboard
2022-09-14 Send off for manufacturing
2022-09-14 Add artwork
2022-09-29 Update gantries based on Lumen V3
2022-09-29 Add x-gantry-block-mount
2022-09-29 Add z-gantry with mounting holes for extra stuff
2022-09-29 Add drag chain mounts
2022-09-29 Add STEP version of Jellyfish's PCB
2022-09-29 Add assembly
2022-10-14 Update license on all hardware files
2022-10-14 Update all LICENSE files and add a simple README
2022-10-14 Fix I2C connections
2022-11-04 starfish: fix input diode value
2022-11-04 starfish: change pin shape
2022-11-04 starfish: fix diode values
2022-11-04 starfish: update mosfet value and rating
2022-11-04 starfish: minor change to text size
2022-11-04 starfish: update BOM values
2022-11-04 Add note about no support
2022-11-28 Add block mount w/ proximity sensor
2022-12-06 Starfish v1
    - Switch from DRV120 smart solenoid drivers to MOSFETs so that a wider variety of solenoids can be controlled. RP2040 PWM should be used along with these MOSFETs to prevent solenoids from overheating.
    - Move all power lines out of inner copper layers and onto back copper.
    - Small changes to signal routing to accommodate new power routing.
2022-12-19 starfish: remove feeder header and use screw terminals for rs-485
2022-12-19 remove drv103 and drv120 breakouts
2022-12-19 Add RS-485 to feeder board
